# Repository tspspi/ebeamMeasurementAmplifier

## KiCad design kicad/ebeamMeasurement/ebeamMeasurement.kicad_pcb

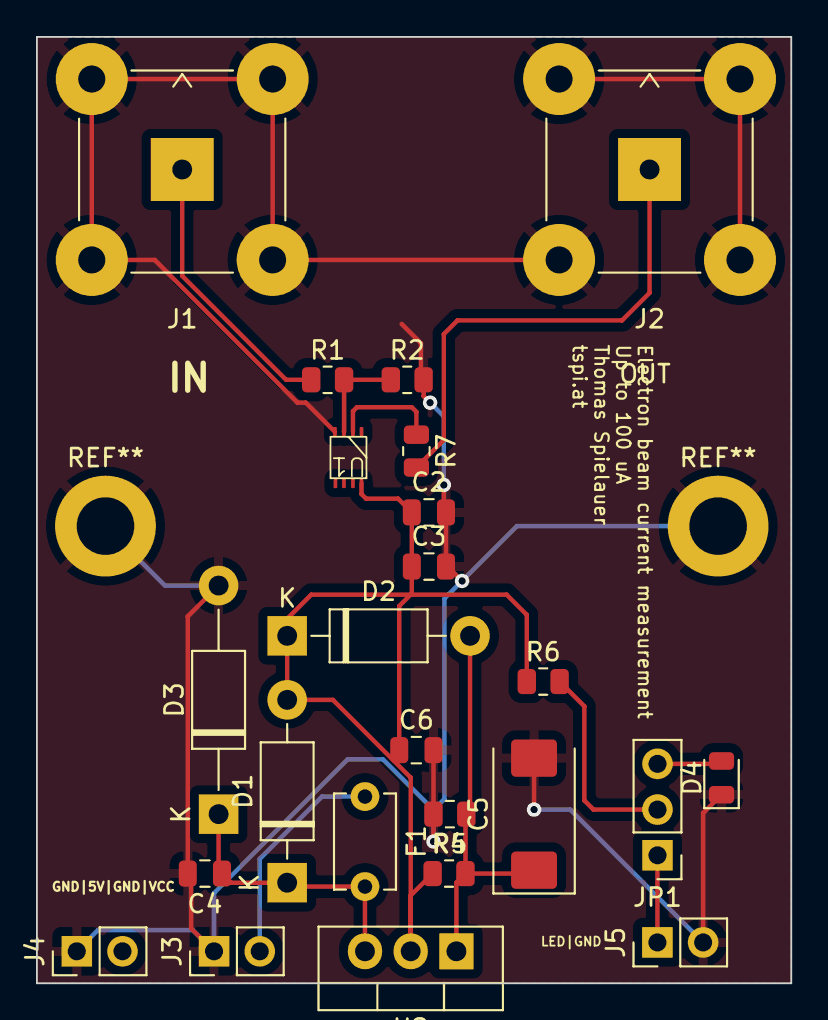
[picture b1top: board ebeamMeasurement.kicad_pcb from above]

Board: 2 copper layers, 41.9 x 52.6 mm, 24 parts (0 on the bottom side), 12 nets.

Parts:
C2: 100pF; C_0805_2012Metric
C3, C6: 1uF; C_0805_2012Metric
C4: 0.1uF; C_0805_2012Metric
C5: 10uF; CP_EIA-7343-20_Kemet-V
D1, D2: 1N4002; D_DO-41_SOD81_P10.16mm_Horizontal
D3: 1N5360BRLG; D_DO-41_SOD81_P12.70mm_Horizontal
D4: LED_PWR; LED_0805_2012Metric
F1: Polyfuse; C_Disc_D5.1mm_W3.2mm_P5.00mm
J1: BeamIn; BNC_TEConnectivity_1478035_Horizontal
J2: Conn_Coaxial; BNC_TEConnectivity_1478035_Horizontal
J3: PWR; PinHeader_1x02_P2.54mm_Vertical
J4: PWR5; PinHeader_1x02_P2.54mm_Vertical
J5: EXT_LED_PWR; PinHeader_1x02_P2.54mm_Vertical
JP1: PWRLEDSELECT; PinHeader_1x03_P2.54mm_Vertical
R1, R2: 50k; R_0805_2012Metric
R4: 240R; R_0805_2012Metric
R5: 720R; R_0805_2012Metric
R6: 100R; R_0805_2012Metric
R7: 10R; R_0805_2012Metric
U1: VSSOP_OPA300
U2: LM317_TO-220; TO-220-3_Vertical

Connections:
+5V: C2.1, C3.1, C6.1, D1.2 (A), D2.1 (K), J4.2, R4.1, R6.1, U1.8 (V+), U2.2 (VO)
GND: C2.2, C3.2, C4.2, C5.2, C6.2, D3.2 (A), D4.1 (K), J1.2 (Ext), J2.2 (Ext), J3.1, J4.1, J5.2, R2.2, R5.2, U1.4 (V-)
unnamed: C4.1, D1.1 (K), D3.1 (K), F1.2, U2.3 (VI)
unnamed: C5.1, D2.2 (A), R4.2, R5.1, U2.1 (ADJ)
unnamed: D4.2 (A), JP1.3 (B)
unnamed: J1.1 (In), R1.1
unnamed: J2.1 (In), R7.2
unnamed: J5.1, JP1.1 (A)
unnamed: JP1.2 (C), R6.2
unnamed: R1.2, R2.1, U1.3 (+)
unnamed: R7.1, U1.1, U1.2 (-)
VCC: F1.1, J3.2
